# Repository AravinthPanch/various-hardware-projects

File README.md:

# various-hardware-projects
Collection of various PCB designs and Firmware for prototyping projects

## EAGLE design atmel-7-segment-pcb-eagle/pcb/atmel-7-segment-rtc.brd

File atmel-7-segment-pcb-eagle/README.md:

Seven Segment Real Time Clock using Atmel
==================================================================

AUTHOR
--------------------------------------
- Aravinth Panchadcharam <http://aravinth.info>

CIRCUIT DESIGN
--------------------------------------

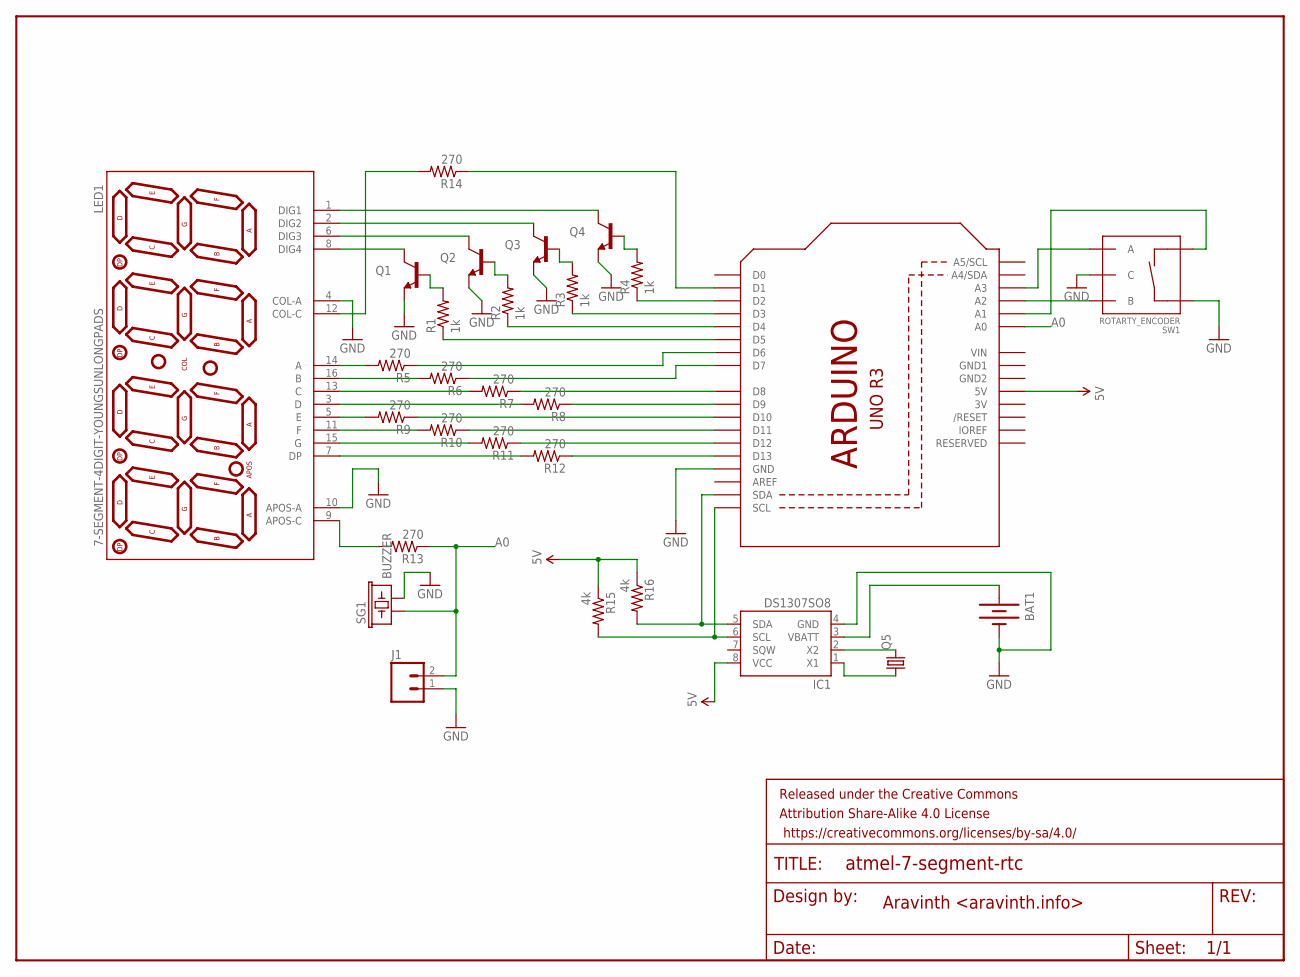
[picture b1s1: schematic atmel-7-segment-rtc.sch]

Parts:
ARDUINO: ARDUINOR3-DIMENSION; ARDUINOR3
BAT1: BATTERY12MM; BATTCON_12MM
FRAME1: FRAME-LETTER; CREATIVE_COMMONS
IC1: DS1307SO8; SO08
J1: M023.5MM; SCREWTERMINAL-3.5MM-2
LED1: 7-SEGMENT-4DIGIT-YOUNGSUNLONGPADS; 7-SEGMENT-4DIGIT-YOUNGSUN-LONGPADS
Q1, Q2, Q3, Q4: TRANSISTOR_NPNMMBT2222A; SOT23-3
Q5: CRYSTALTC26H; TC26H
R1, R2, R3, R4: 1k; 0805
R5, R6, R7, R8, R9, R10, R11, R12, R13, R14: 270; 0805
R15, R16: 4k; 0805
SG1: BUZZER; BUZZER-12MM-NS
SW1: ROTARTY_ENCODER; ROTARY_ENC_PLAIN

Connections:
3V: ARDUINO.3V
5V: ARDUINO.5V, IC1.8 (VCC), R15.1, R16.1
A0: ARDUINO.A0, J1.2, R13.1, SG1.+ (1)
GND: ARDUINO.GND, BAT1.GND (-), IC1.4 (GND), J1.1, LED1.4 (COL-A), LED1.10 (APOS-A), Q1.2 (E), Q2.2 (E), Q3.2 (E), Q4.2 (E), SG1.- (2), SW1.C, SW1.SW+
GND1: ARDUINO.GND1
GND2: ARDUINO.GND2
unnamed: ARDUINO.D5, R1.1
unnamed: Q1.1 (B), R1.2
unnamed: Q2.1 (B), R2.2
unnamed: Q3.1 (B), R3.2
unnamed: LED1.8 (DIG4), Q1.3 (C)
unnamed: LED1.6 (DIG3), Q2.3 (C)
unnamed: LED1.2 (DIG2), Q3.3 (C)
unnamed: LED1.1 (DIG1), Q4.3 (C)
unnamed: Q4.1 (B), R4.2
unnamed: ARDUINO.D2, R4.1
unnamed: ARDUINO.D3, R3.1
unnamed: ARDUINO.D4, R2.1
unnamed: LED1.12 (COL-C), R14.2
unnamed: ARDUINO.D1, R14.1
unnamed: LED1.14 (A), R5.2
unnamed: LED1.16 (B), R6.2
unnamed: LED1.13 (C), R7.2
unnamed: LED1.3 (D), R8.2
unnamed: LED1.5 (E), R9.2
unnamed: LED1.11 (F), R10.2
unnamed: LED1.15 (G), R11.2
unnamed: LED1.7 (DP), R12.2
unnamed: ARDUINO.D6, R5.1
unnamed: ARDUINO.D7, R6.1
unnamed: ARDUINO.D8, R7.1
unnamed: ARDUINO.D9, R8.1
unnamed: ARDUINO.D10, R9.1
unnamed: ARDUINO.D11, R10.1
unnamed: ARDUINO.D12, R11.1
unnamed: ARDUINO.D13, R12.1
unnamed: ARDUINO.SDA, IC1.5 (SDA), R16.2
unnamed: LED1.9 (APOS-C), R13.2
unnamed: ARDUINO.SCL, IC1.6 (SCL), R15.2
unnamed: ARDUINO.A2, SW1.B
unnamed: IC1.2 (X2), Q5.2
unnamed: IC1.1 (X1), Q5.1
unnamed: BAT1.PWR@1 (+), IC1.3 (VBATT)
unnamed: ARDUINO.A1, SW1.SW-
unnamed: ARDUINO.A3, SW1.A
VIN: ARDUINO.VIN

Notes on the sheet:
Aravinth <aravinth.info>

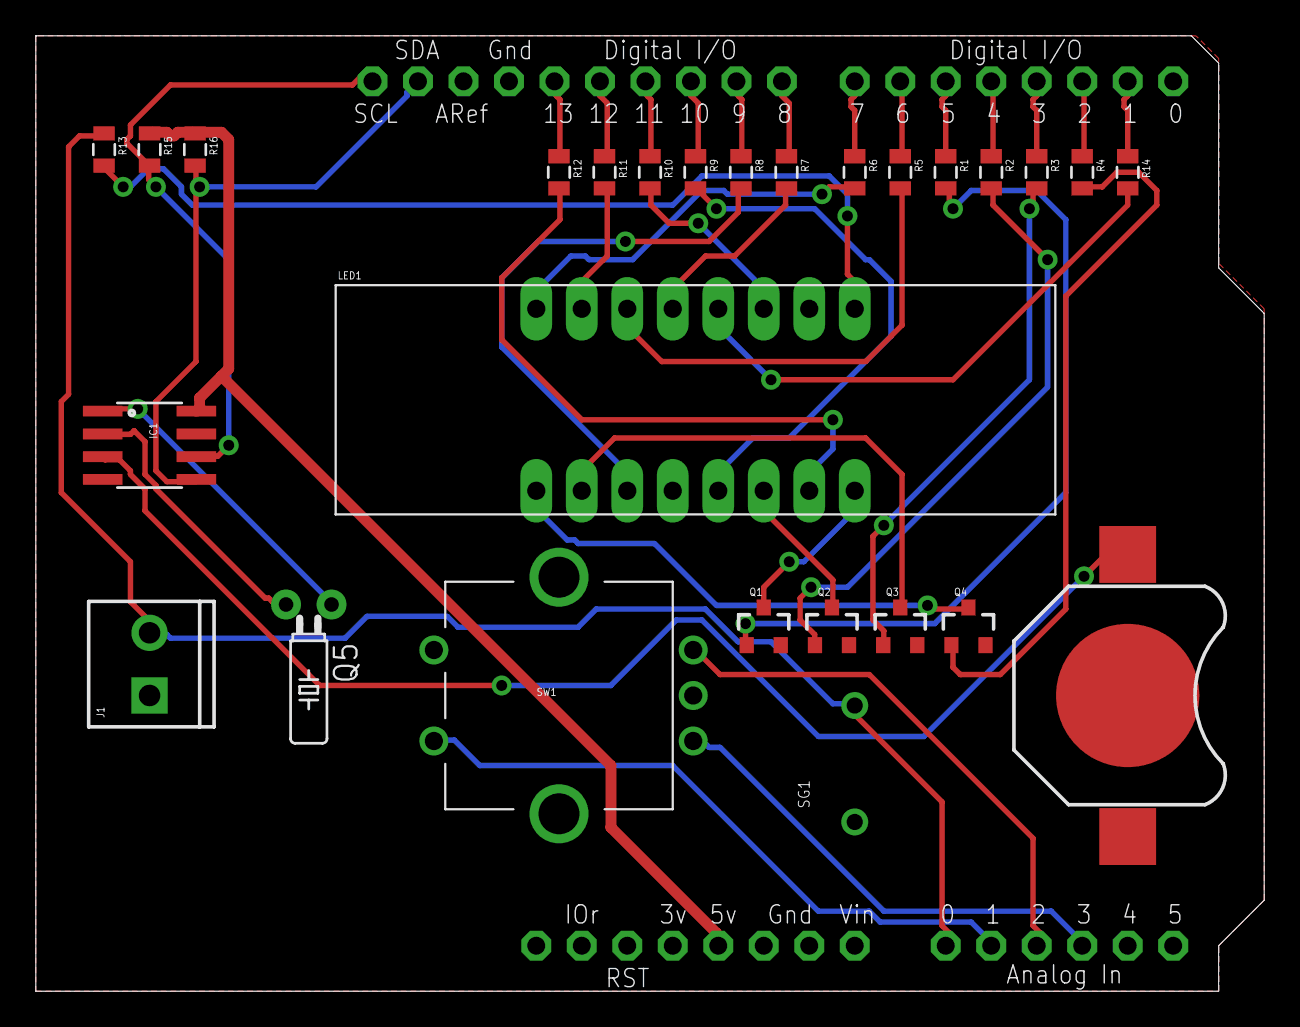
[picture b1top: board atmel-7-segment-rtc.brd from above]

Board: 2 copper layers, 68.6 x 53.3 mm, 29 parts (0 on the bottom side), 42 nets.

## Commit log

2017-08-27 Add LED PWM Lamp prototypes and Electron App
2018-10-29 Add arabeat atmega2560 project
2018-10-29 Add atmega baseboard
2018-10-29 Add test board for IPKF machine
2018-10-29 Add nano led matrix
2019-01-04 Add LPKF test PCB, clean files
2019-01-12 Add SMD test pcb for LPKF
2019-07-09 Add led star project
2019-10-12 Add apache 2.0 opensource licence
2020-07-07 Bump electron in /led-lamp-proto/proto-2/lamp_tx_electron_app
    Bumps [electron](https://github.com/electron/electron) from 1.8.8 to 9.1.0.
    - [Release notes](https://github.com/electron/electron/releases)
    - [Changelog](https://github.com/electron/electron/blob/master/docs/breaking-changes.md)
    - [Commits](https://github.com/electron/electron/compare/v1.8.8...v9.1.0)
2021-03-29 Add Ad5933 prototype
2022-05-02 Add qm qpc blinky
2022-05-04 Add STM32 L152RE Nuclueo
2022-05-05 Add startup training project
2022-05-05 Update qm blinky
2022-05-05 Add dpp example for nucleo-l152re
2022-05-05 Clean up dpp example
2022-05-05 Update gitignore

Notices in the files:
parts and their libraries:
SparkFun-Electromechanical: Licensing: Creative Commons ShareAlike 4.0 International - https://creativecommons.org/licenses/by-sa/4.0
SparkFun-Aesthetics: Released under the Creative Commons Attribution Share-Alike 4.0 License
SparkFun-Aesthetics: https://creativecommons.org/licenses/by-sa/4.0
